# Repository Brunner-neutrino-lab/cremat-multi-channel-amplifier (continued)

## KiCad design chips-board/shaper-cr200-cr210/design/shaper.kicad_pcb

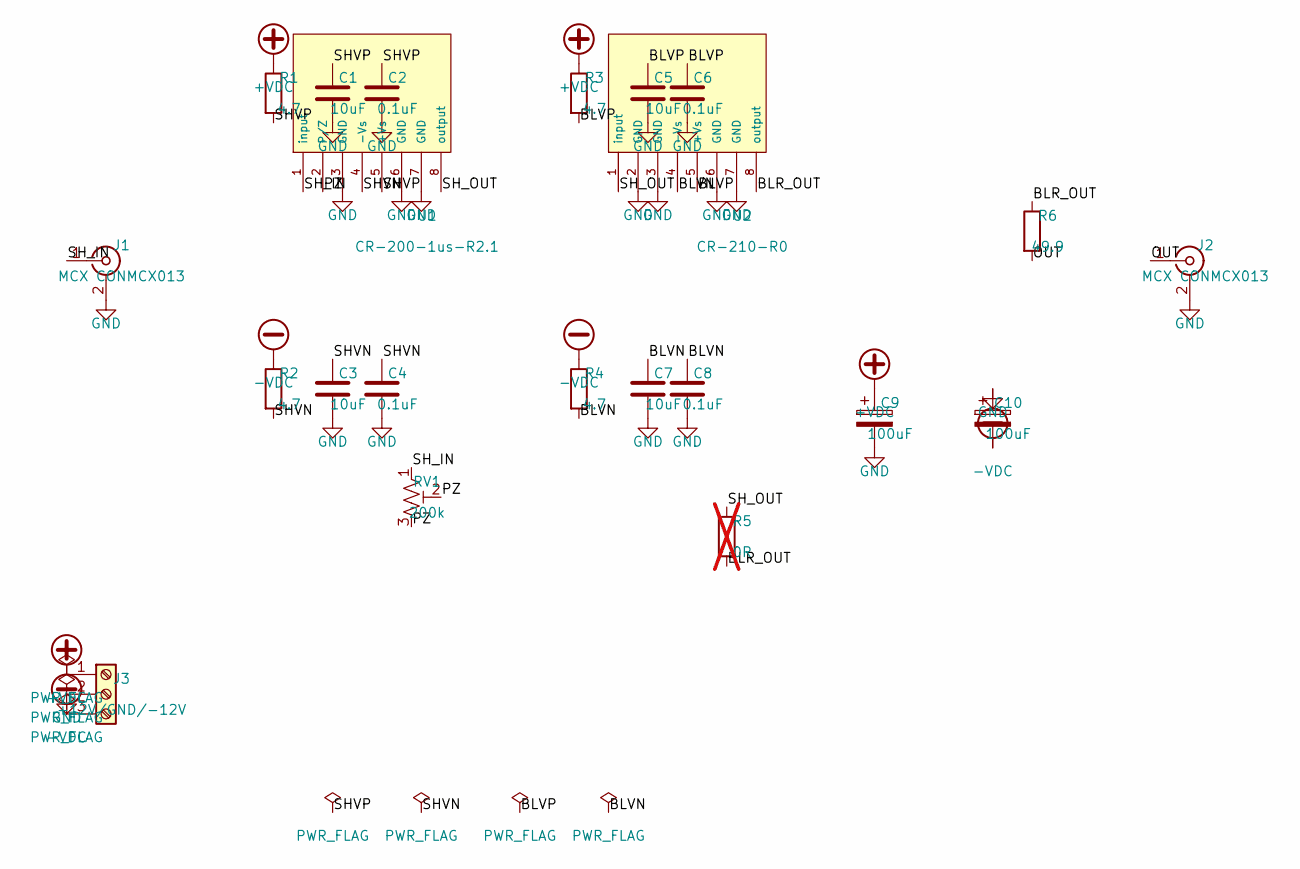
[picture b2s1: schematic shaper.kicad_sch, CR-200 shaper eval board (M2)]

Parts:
C1, C3, C5, C7: 10uF; C_0805_2012Metric; MPN CL21A106KAYNNNE
C2, C4, C6, C8: 0.1uF; C_0805_2012Metric; MPN CL21B104KBCNNNC
C9, C10: 100uF; CP_Elec_6.3x7.7; MPN UWT1V101MCL1GS
J1, J2: MCX CONMCX013; MCX_CONMCX013_EdgeMount; MPN CONMCX013
J3: +12V/GND/-12V; TerminalBlock_Phoenix_MKDS-1,5-3_1x03_P5.00mm_Horizontal; MPN 1715734
R1, R2, R3, R4: 4.7; R_0805_2012Metric; MPN RC0805JR-074R7L
R5: 0R; R_0805_2012Metric; MPN RC0805JR-070RL; not fitted
R6: 49.9; R_0805_2012Metric; MPN RC0805FR-0749R9L
RV1: 200k; Potentiometer_Bourns_3296W_Vertical; MPN 3296W-1-204LF
U1: CR-200-1us-R2.1; PinHeader_1x08_P2.54mm_Vertical; MPN CR-200-1us-R2.1
U2: CR-210-R0; PinHeader_1x08_P2.54mm_Vertical; MPN CR-210-R0

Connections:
+VDC: C9.1, J3.1, R1.1, R3.1
-VDC: C10.2, J3.3, R2.1, R4.1
BLR_OUT: R5.2, R6.1, U2.8 (output)
BLVN: C7.1, C8.1, R4.2, U2.4 (-Vs)
BLVP: C5.1, C6.1, R3.2, U2.5 (+Vs)
GND: C1.2, C2.2, C3.2, C4.2, C5.2, C6.2, C7.2, C8.2, C9.2, C10.1, J1.2 (Ext), J2.2 (Ext), J3.2, U1.3 (GND), U1.6 (GND), U1.7 (GND), U2.2 (GND), U2.3 (GND), U2.6 (GND), U2.7 (GND)
OUT: J2.1 (In), R6.2
PZ: RV1.2, RV1.3, U1.2 (P/Z)
SHVN: C3.1, C4.1, R2.2, U1.4 (-Vs)
SHVP: C1.1, C2.1, R1.2, U1.5 (+Vs)
SH_IN: J1.1 (In), RV1.1, U1.1 (input)
SH_OUT: R5.1, U1.8 (output), U2.1 (input)

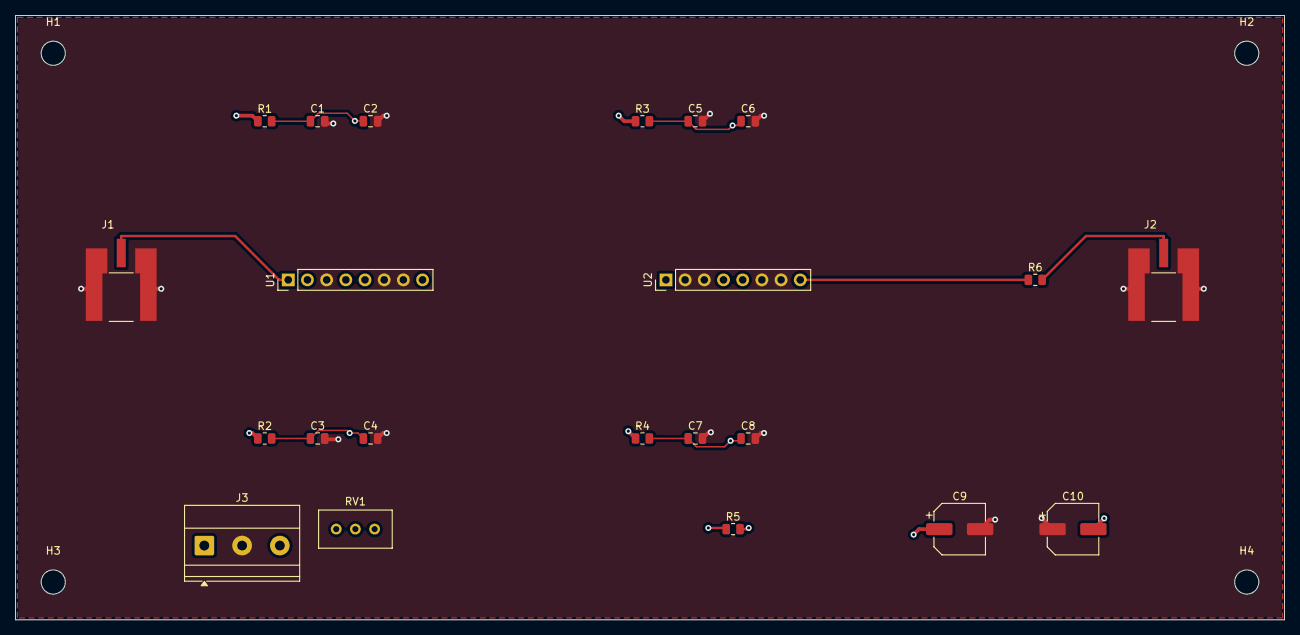
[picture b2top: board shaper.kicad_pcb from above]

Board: 4 copper layers, 168.0 x 80.0 mm, 26 parts (0 on the bottom side), 12 nets.

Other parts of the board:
H1, H2, H3, H4: MountingHole_3.2mm_M3

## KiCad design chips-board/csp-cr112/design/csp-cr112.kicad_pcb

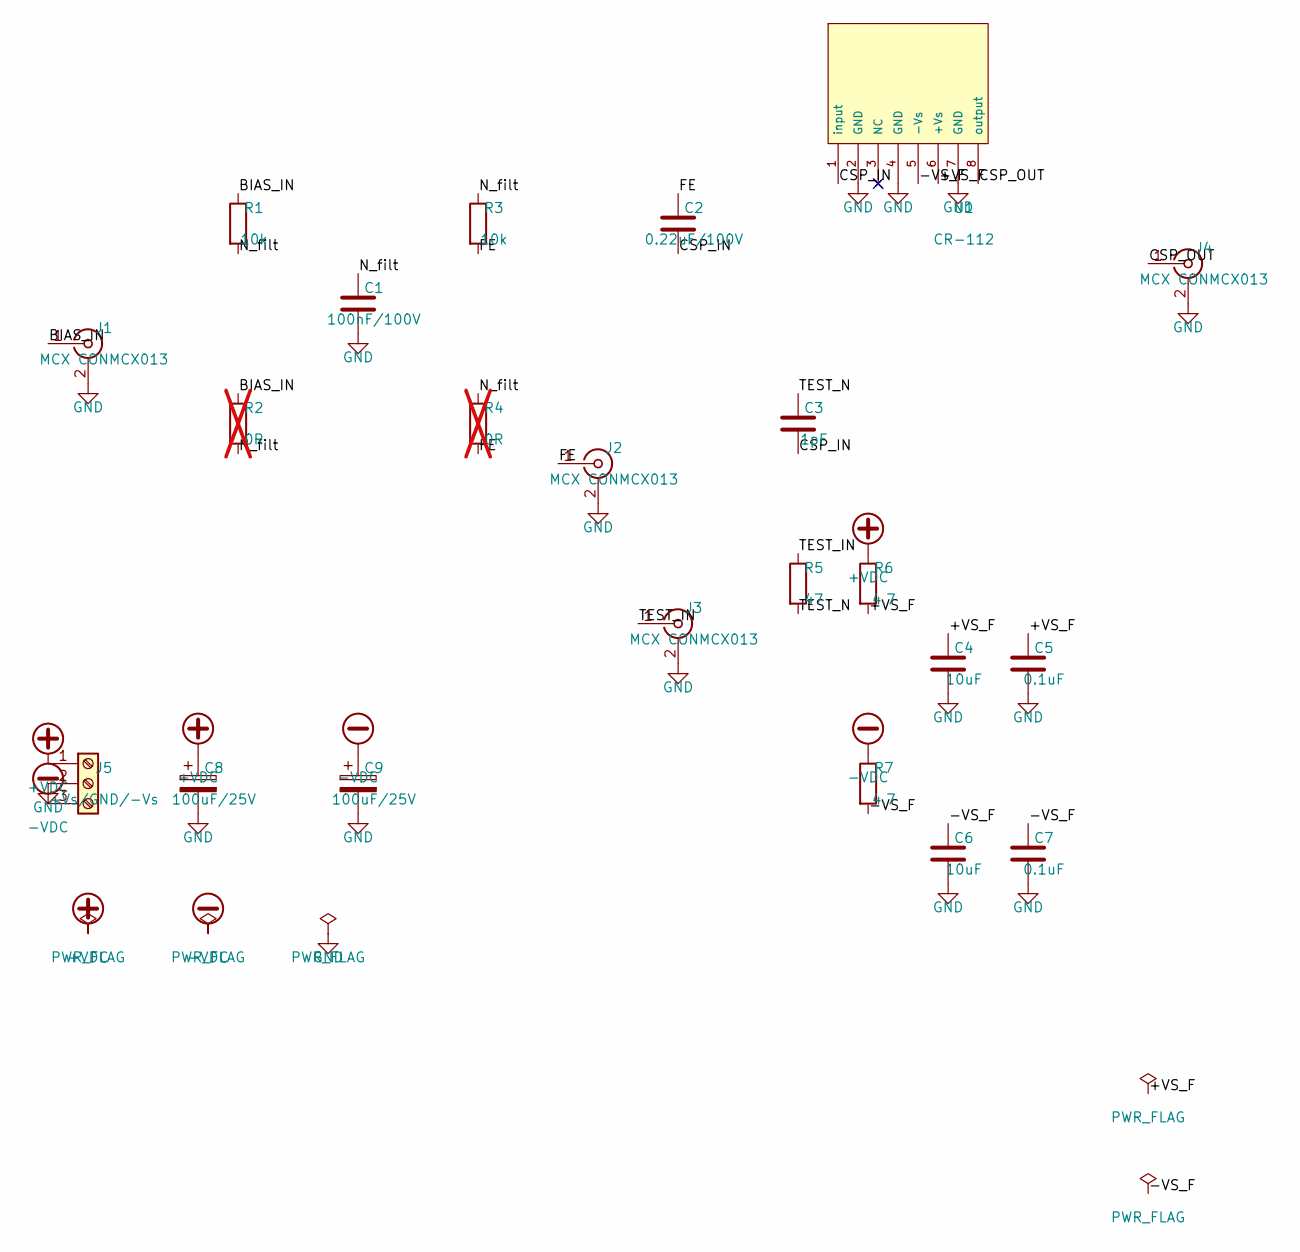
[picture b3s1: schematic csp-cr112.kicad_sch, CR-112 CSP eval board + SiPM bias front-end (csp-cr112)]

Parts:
C1: 100nF/100V; C_0805_2012Metric; MPN CL21B104KCC5PNC
C2: 0.22uF/100V; C_0805_2012Metric; MPN GRM21AR72A224KAC5K
C3: 1pF; C_0805_2012Metric; MPN CC0805CRNPO9BN1R0
C4, C6: 10uF; C_0805_2012Metric; MPN CL21A106KAYNNNE
C5, C7: 0.1uF; C_0805_2012Metric; MPN CL21B104KBCNNNC
C8, C9: 100uF/25V; CP_Radial_D6.3mm_P2.50mm; MPN UVR1E101MED
J1, J2, J3, J4: MCX CONMCX013; MCX_CONMCX013_EdgeMount; MPN CONMCX013
J5: +Vs/GND/-Vs; TerminalBlock_Phoenix_MKDS-1,5-3_1x03_P5.00mm_Horizontal; MPN 1715035
R1, R3: 10k; R_0805_2012Metric; MPN RC0805FR-0710KL
R2, R4: 0R; R_0805_2012Metric; MPN RC0805JR-070RL; not fitted
R5: 47; R_0805_2012Metric; MPN RC0805JR-0747RL
R6, R7: 4.7; R_0805_2012Metric; MPN RC0805JR-074R7L
U1: CR-112; PinHeader_1x08_P2.54mm_Vertical; MPN CR-112-R2.1

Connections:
+VDC: C8.1, J5.1, R6.1
-VDC: C9.1, J5.3, R7.1
/+VS_F: C4.1, C5.1, R6.2, U1.6 (+Vs)
/-VS_F: C6.1, C7.1, R7.2, U1.5 (-Vs)
/BIAS_IN: J1.1 (In), R1.1, R2.1
/CSP_IN: C2.2, C3.2, U1.1 (input)
/CSP_OUT: J4.1 (In), U1.8 (output)
/FE: C2.1, J2.1 (In), R3.2, R4.2
/N_filt: C1.1, R1.2, R2.2, R3.1, R4.1
/TEST_IN: J3.1 (In), R5.1
/TEST_N: C3.1, R5.2
GND: C1.2, C4.2, C5.2, C6.2, C7.2, C8.2, C9.2, J1.2 (Ext), J2.2 (Ext), J3.2 (Ext), J4.2 (Ext), J5.2, U1.2 (GND), U1.4 (GND), U1.7 (GND)

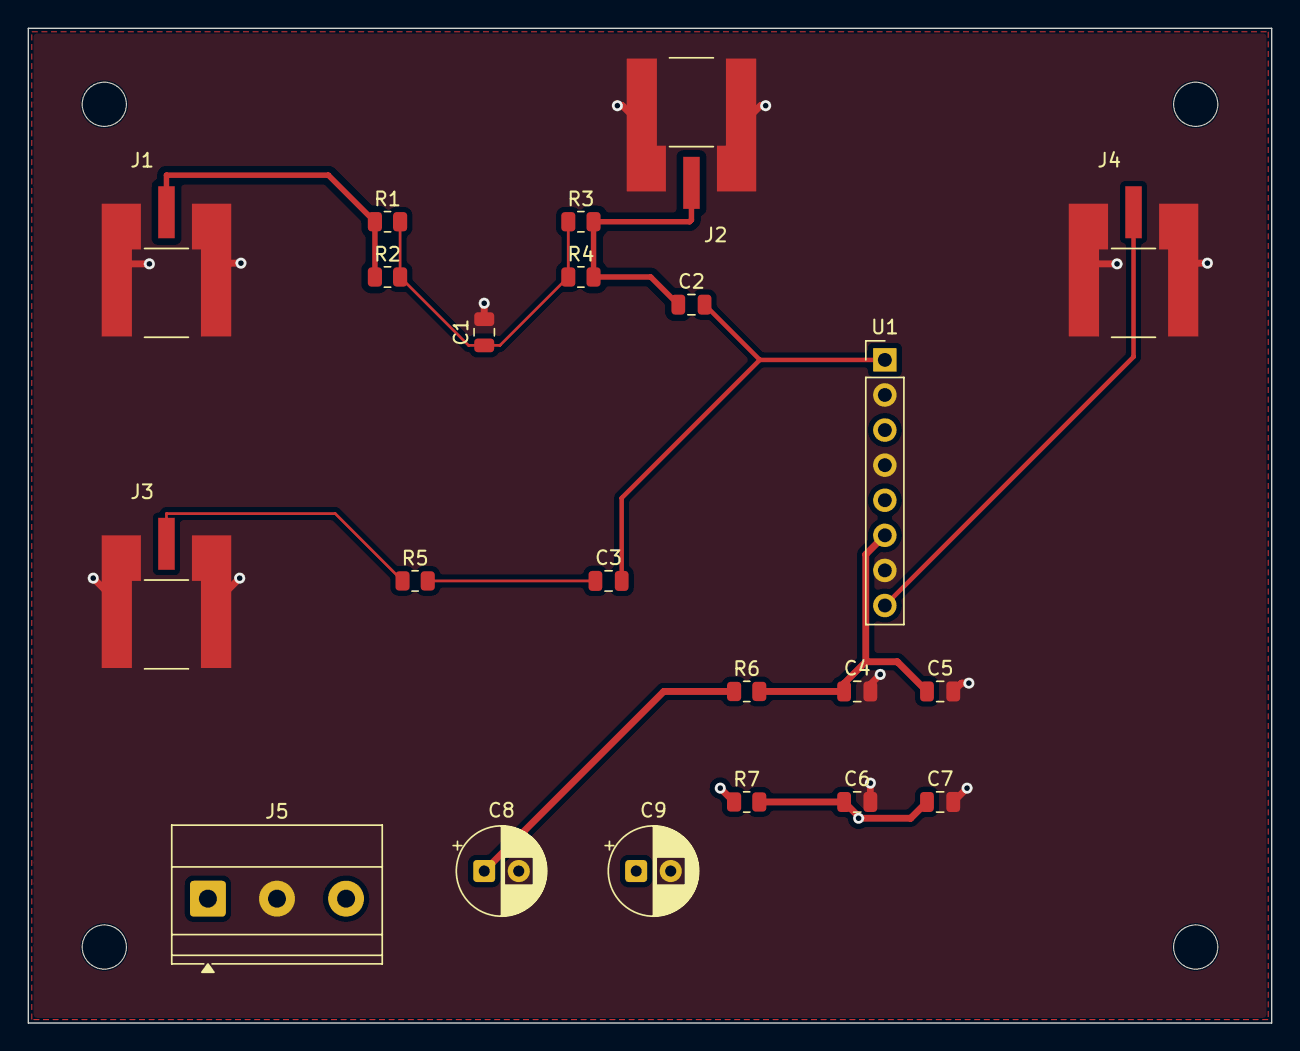
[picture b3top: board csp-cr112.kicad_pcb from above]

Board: 4 copper layers, 90.0 x 72.0 mm, 26 parts (0 on the bottom side), 12 nets.

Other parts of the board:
H1, H2, H3, H4: MountingHole_3.2mm_M3

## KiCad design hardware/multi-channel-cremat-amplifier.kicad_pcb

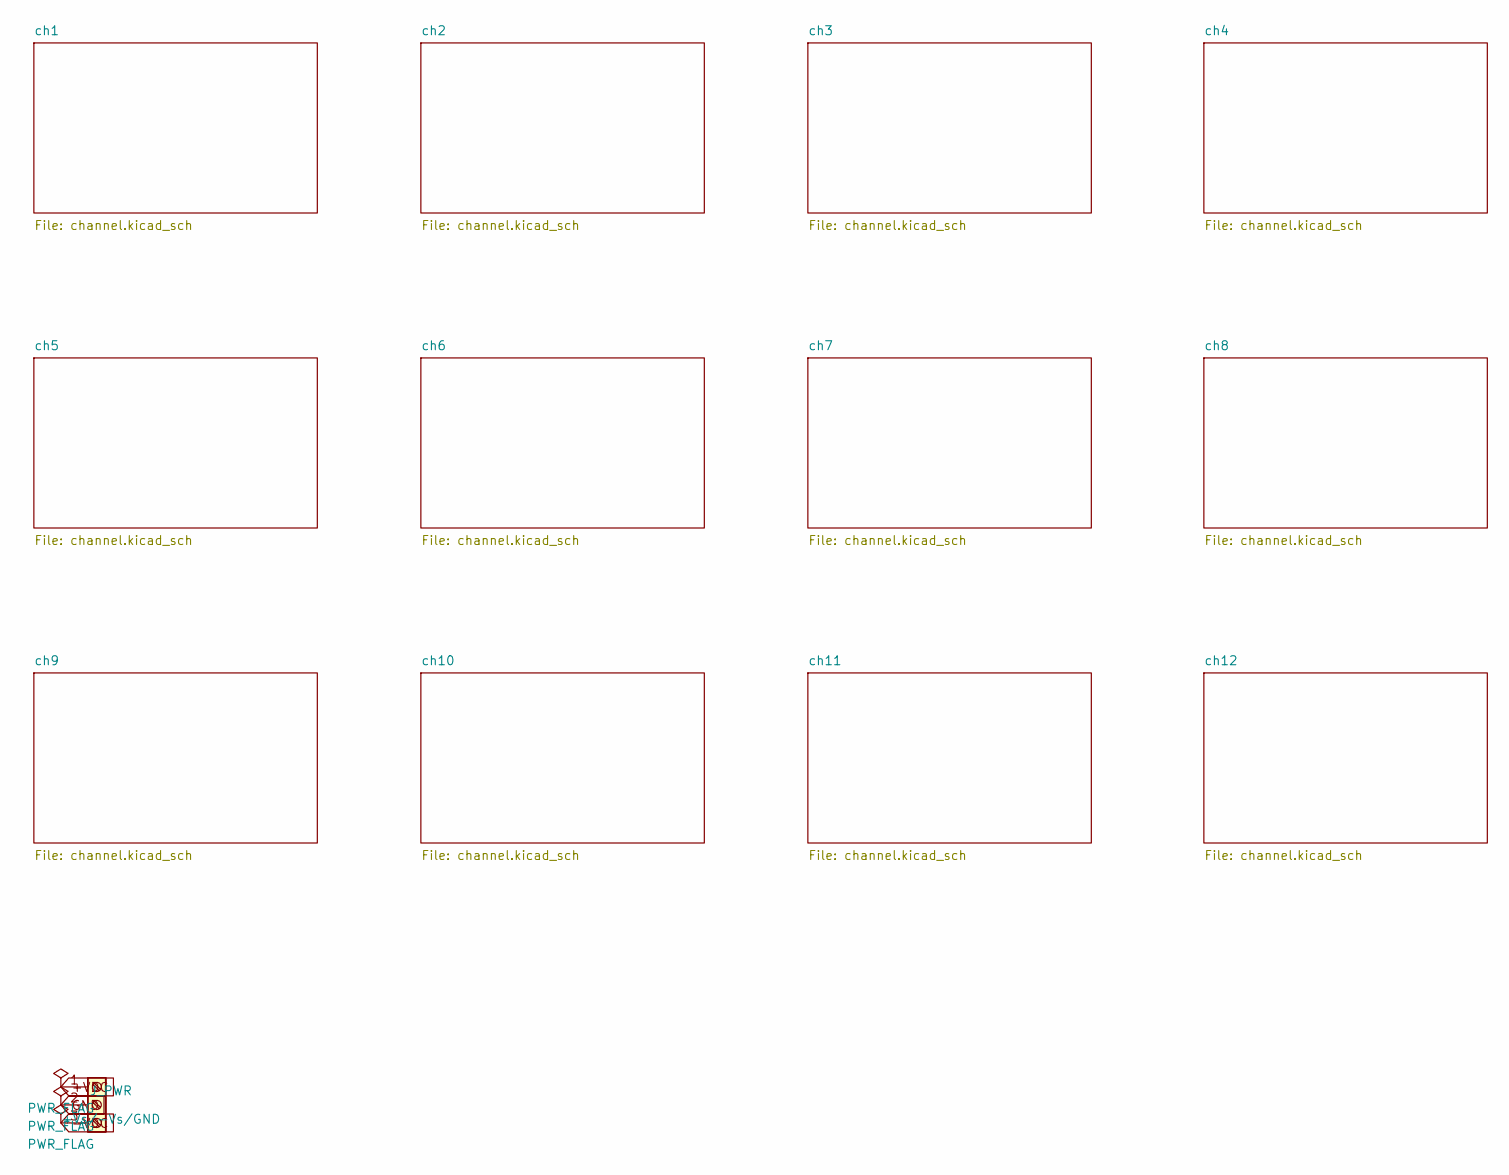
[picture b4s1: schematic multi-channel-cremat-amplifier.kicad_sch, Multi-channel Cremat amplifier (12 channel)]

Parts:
J_PWR: +Vs/-Vs/GND; TerminalBlock_Phoenix_MKDS-1,5-3_1x03_P5.00mm_Horizontal

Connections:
+VDC: J_PWR.1; also elsewhere on the board
-VDC: J_PWR.3; also elsewhere on the board
GND: J_PWR.2; also elsewhere on the board

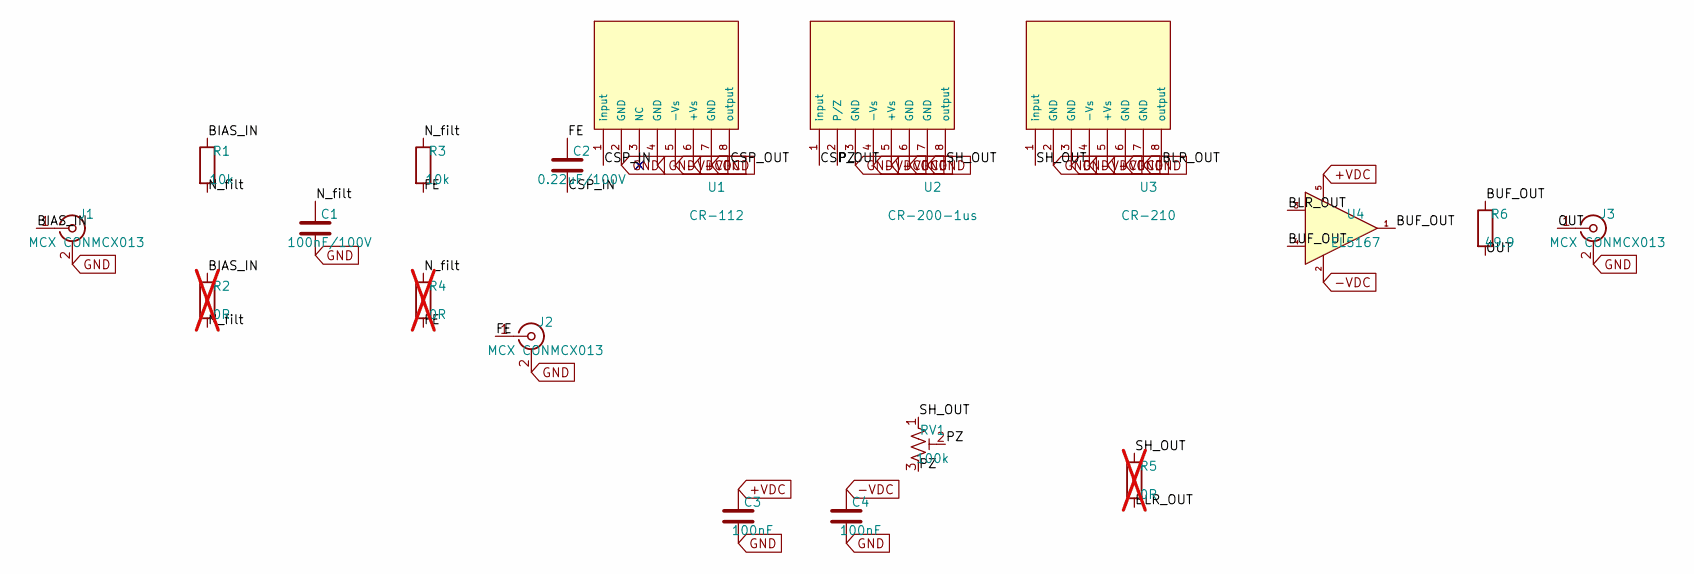
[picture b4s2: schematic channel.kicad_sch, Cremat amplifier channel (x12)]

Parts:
C1: 100nF/100V; C_0805_2012Metric
C2: 0.22uF/100V; C_0805_2012Metric
C3, C4: 100nF; C_0805_2012Metric
J1, J2, J3: MCX CONMCX013; MCX_CONMCX013_EdgeMount
R1, R3: 10k; R_0805_2012Metric
R2, R4, R5: 0R; R_0805_2012Metric; not fitted
R6: 49.9; R_0805_2012Metric
RV1: 100k; Potentiometer_Bourns_3296W_Vertical
U1: CR-112; PinHeader_1x08_P2.54mm_Vertical
U2: CR-200-1us; PinHeader_1x08_P2.54mm_Vertical
U3: CR-210; PinHeader_1x08_P2.54mm_Vertical
U4: EL5167; SOT-23-5

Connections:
+VDC: C3.1, U1.6 (+Vs), U2.5 (+Vs), U3.5 (+Vs), U4.5 (V+); also elsewhere on the board
-VDC: C4.1, U1.5 (-Vs), U2.4 (-Vs), U3.4 (-Vs), U4.2 (V-); also elsewhere on the board
/ch1/BIAS_IN: J1.1 (In), R1.1, R2.1
/ch1/BLR_OUT: R5.2, U3.8 (output), U4.3 (+)
/ch1/BUF_OUT: R6.1, U4.1, U4.4 (-)
/ch1/CSP_IN: C2.2, U1.1 (input)
/ch1/CSP_OUT: U1.8 (output), U2.1 (input)
/ch1/FE: C2.1, J2.1 (In), R3.2, R4.2
/ch1/N_filt: C1.1, R1.2, R2.2, R3.1, R4.1
/ch1/OUT: J3.1 (In), R6.2
/ch1/PZ: RV1.2, RV1.3, U2.2 (P/Z)
/ch1/SH_OUT: R5.1, RV1.1, U2.8 (output), U3.1 (input)
GND: C1.2, C3.2, C4.2, J1.2 (Ext), J2.2 (Ext), J3.2 (Ext), U1.2 (GND), U1.4 (GND), U1.7 (GND), U2.3 (GND), U2.6 (GND), U2.7 (GND), U3.2 (GND), U3.3 (GND), U3.6 (GND), U3.7 (GND); also elsewhere on the board

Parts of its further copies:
C5, C9, C13, C17, C21, C25, C29, C33, C37, C41, C45: 100nF/100V; C_0805_2012Metric
C6, C10, C14, C18, C22, C26, C30, C34, C38, C42, C46: 0.22uF/100V; C_0805_2012Metric
C7, C8, C11, C12, C15, C16, C19, C20, C23, C24, C27, C28, C31, C32, C35, C36, C39, C40, C43, C44, C47, C48: 100nF; C_0805_2012Metric
J4, J5, J6, J7, J8, J9, J10, J11, J12, J13, J14, J15, J16, J17, J18, J19, J20, J21, J22, J23, J24, J25, J26, J27, J28, J29, J30, J31, J32, J33, J34, J35, J36: MCX CONMCX013; MCX_CONMCX013_EdgeMount
R7, R9, R13, R15, R19, R21, R25, R27, R31, R33, R37, R39, R43, R45, R49, R51, R55, R57, R61, R63, R67, R69: 10k; R_0805_2012Metric
R8, R10, R11, R14, R16, R17, R20, R22, R23, R26, R28, R29, R32, R34, R35, R38, R40, R41, R44, R46, R47, R50, R52, R53, R56, R58, R59, R62, R64, R65, R68, R70, R71: 0R; R_0805_2012Metric; not fitted
R12, R18, R24, R30, R36, R42, R48, R54, R60, R66, R72: 49.9; R_0805_2012Metric
RV2, RV3, RV4, RV5, RV6, RV7, RV8, RV9, RV10, RV11, RV12: 100k; Potentiometer_Bourns_3296W_Vertical
U5, U9, U13, U17, U21, U25, U29, U33, U37, U41, U45: CR-112; PinHeader_1x08_P2.54mm_Vertical
U6, U10, U14, U18, U22, U26, U30, U34, U38, U42, U46: CR-200-1us; PinHeader_1x08_P2.54mm_Vertical
U7, U11, U15, U19, U23, U27, U31, U35, U39, U43, U47: CR-210; PinHeader_1x08_P2.54mm_Vertical
U8, U12, U16, U20, U24, U28, U32, U36, U40, U44, U48: EL5167; SOT-23-5

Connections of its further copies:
+VDC: C7.1, C11.1, C15.1, C19.1, C23.1, C27.1, C31.1, C35.1, C39.1, C43.1, C47.1, U5.6 (+Vs), U6.5 (+Vs), U7.5 (+Vs), U8.5 (V+), U9.6 (+Vs), U10.5 (+Vs), U11.5 (+Vs), U12.5 (V+), U13.6 (+Vs), U14.5 (+Vs), U15.5 (+Vs), U16.5 (V+), U17.6 (+Vs), U18.5 (+Vs), U19.5 (+Vs), U20.5 (V+), U21.6 (+Vs), U22.5 (+Vs), U23.5 (+Vs), U24.5 (V+), U25.6 (+Vs), U26.5 (+Vs), U27.5 (+Vs), U28.5 (V+), U29.6 (+Vs), U30.5 (+Vs), U31.5 (+Vs), U32.5 (V+), U33.6 (+Vs), U34.5 (+Vs), U35.5 (+Vs), U36.5 (V+), U37.6 (+Vs), U38.5 (+Vs), U39.5 (+Vs), U40.5 (V+), U41.6 (+Vs), U42.5 (+Vs), U43.5 (+Vs), U44.5 (V+), U45.6 (+Vs), U46.5 (+Vs), U47.5 (+Vs), U48.5 (V+); also elsewhere on the board
-VDC: C8.1, C12.1, C16.1, C20.1, C24.1, C28.1, C32.1, C36.1, C40.1, C44.1, C48.1, U5.5 (-Vs), U6.4 (-Vs), U7.4 (-Vs), U8.2 (V-), U9.5 (-Vs), U10.4 (-Vs), U11.4 (-Vs), U12.2 (V-), U13.5 (-Vs), U14.4 (-Vs), U15.4 (-Vs), U16.2 (V-), U17.5 (-Vs), U18.4 (-Vs), U19.4 (-Vs), U20.2 (V-), U21.5 (-Vs), U22.4 (-Vs), U23.4 (-Vs), U24.2 (V-), U25.5 (-Vs), U26.4 (-Vs), U27.4 (-Vs), U28.2 (V-), U29.5 (-Vs), U30.4 (-Vs), U31.4 (-Vs), U32.2 (V-), U33.5 (-Vs), U34.4 (-Vs), U35.4 (-Vs), U36.2 (V-), U37.5 (-Vs), U38.4 (-Vs), U39.4 (-Vs), U40.2 (V-), U41.5 (-Vs), U42.4 (-Vs), U43.4 (-Vs), U44.2 (V-), U45.5 (-Vs), U46.4 (-Vs), U47.4 (-Vs), U48.2 (V-); also elsewhere on the board
/ch2/BIAS_IN: J4.1 (In), R7.1, R8.1
/ch2/BLR_OUT: R11.2, U7.8 (output), U8.3 (+)
/ch2/BUF_OUT: R12.1, U8.1, U8.4 (-)
/ch2/CSP_IN: C6.2, U5.1 (input)
/ch2/CSP_OUT: U5.8 (output), U6.1 (input)
/ch2/FE: C6.1, J5.1 (In), R9.2, R10.2
/ch2/N_filt: C5.1, R7.2, R8.2, R9.1, R10.1
/ch2/OUT: J6.1 (In), R12.2
/ch2/PZ: RV2.2, RV2.3, U6.2 (P/Z)
/ch2/SH_OUT: R11.1, RV2.1, U6.8 (output), U7.1 (input)
/ch3/BIAS_IN: J7.1 (In), R13.1, R14.1
/ch3/BLR_OUT: R17.2, U11.8 (output), U12.3 (+)
/ch3/BUF_OUT: R18.1, U12.1, U12.4 (-)
/ch3/CSP_IN: C10.2, U9.1 (input)
/ch3/CSP_OUT: U9.8 (output), U10.1 (input)
/ch3/FE: C10.1, J8.1 (In), R15.2, R16.2
/ch3/N_filt: C9.1, R13.2, R14.2, R15.1, R16.1
/ch3/OUT: J9.1 (In), R18.2
/ch3/PZ: RV3.2, RV3.3, U10.2 (P/Z)
/ch3/SH_OUT: R17.1, RV3.1, U10.8 (output), U11.1 (input)
/ch4/BIAS_IN: J10.1 (In), R19.1, R20.1
/ch4/BLR_OUT: R23.2, U15.8 (output), U16.3 (+)
/ch4/BUF_OUT: R24.1, U16.1, U16.4 (-)
/ch4/CSP_IN: C14.2, U13.1 (input)
/ch4/CSP_OUT: U13.8 (output), U14.1 (input)
/ch4/FE: C14.1, J11.1 (In), R21.2, R22.2
/ch4/N_filt: C13.1, R19.2, R20.2, R21.1, R22.1
/ch4/OUT: J12.1 (In), R24.2
/ch4/PZ: RV4.2, RV4.3, U14.2 (P/Z)
/ch4/SH_OUT: R23.1, RV4.1, U14.8 (output), U15.1 (input)
/ch5/BIAS_IN: J13.1 (In), R25.1, R26.1
/ch5/BLR_OUT: R29.2, U19.8 (output), U20.3 (+)
/ch5/BUF_OUT: R30.1, U20.1, U20.4 (-)
/ch5/CSP_IN: C18.2, U17.1 (input)
/ch5/CSP_OUT: U17.8 (output), U18.1 (input)
/ch5/FE: C18.1, J14.1 (In), R27.2, R28.2
/ch5/N_filt: C17.1, R25.2, R26.2, R27.1, R28.1
/ch5/OUT: J15.1 (In), R30.2
/ch5/PZ: RV5.2, RV5.3, U18.2 (P/Z)
/ch5/SH_OUT: R29.1, RV5.1, U18.8 (output), U19.1 (input)
/ch6/BIAS_IN: J16.1 (In), R31.1, R32.1
/ch6/BLR_OUT: R35.2, U23.8 (output), U24.3 (+)
/ch6/BUF_OUT: R36.1, U24.1, U24.4 (-)
/ch6/CSP_IN: C22.2, U21.1 (input)
/ch6/CSP_OUT: U21.8 (output), U22.1 (input)
/ch6/FE: C22.1, J17.1 (In), R33.2, R34.2
/ch6/N_filt: C21.1, R31.2, R32.2, R33.1, R34.1
/ch6/OUT: J18.1 (In), R36.2
/ch6/PZ: RV6.2, RV6.3, U22.2 (P/Z)
/ch6/SH_OUT: R35.1, RV6.1, U22.8 (output), U23.1 (input)
/ch7/BIAS_IN: J19.1 (In), R37.1, R38.1
/ch7/BLR_OUT: R41.2, U27.8 (output), U28.3 (+)
/ch7/BUF_OUT: R42.1, U28.1, U28.4 (-)
/ch7/CSP_IN: C26.2, U25.1 (input)
/ch7/CSP_OUT: U25.8 (output), U26.1 (input)
/ch7/FE: C26.1, J20.1 (In), R39.2, R40.2
/ch7/N_filt: C25.1, R37.2, R38.2, R39.1, R40.1
/ch7/OUT: J21.1 (In), R42.2
/ch7/PZ: RV7.2, RV7.3, U26.2 (P/Z)
/ch7/SH_OUT: R41.1, RV7.1, U26.8 (output), U27.1 (input)
/ch8/BIAS_IN: J22.1 (In), R43.1, R44.1
/ch8/BLR_OUT: R47.2, U31.8 (output), U32.3 (+)
/ch8/BUF_OUT: R48.1, U32.1, U32.4 (-)
/ch8/CSP_IN: C30.2, U29.1 (input)
/ch8/CSP_OUT: U29.8 (output), U30.1 (input)
/ch8/FE: C30.1, J23.1 (In), R45.2, R46.2
/ch8/N_filt: C29.1, R43.2, R44.2, R45.1, R46.1
/ch8/OUT: J24.1 (In), R48.2
/ch8/PZ: RV8.2, RV8.3, U30.2 (P/Z)
/ch8/SH_OUT: R47.1, RV8.1, U30.8 (output), U31.1 (input)
/ch9/BIAS_IN: J25.1 (In), R49.1, R50.1
/ch9/BLR_OUT: R53.2, U35.8 (output), U36.3 (+)
/ch9/BUF_OUT: R54.1, U36.1, U36.4 (-)
/ch9/CSP_IN: C34.2, U33.1 (input)
/ch9/CSP_OUT: U33.8 (output), U34.1 (input)
/ch9/FE: C34.1, J26.1 (In), R51.2, R52.2
/ch9/N_filt: C33.1, R49.2, R50.2, R51.1, R52.1
/ch9/OUT: J27.1 (In), R54.2
/ch9/PZ: RV9.2, RV9.3, U34.2 (P/Z)
/ch9/SH_OUT: R53.1, RV9.1, U34.8 (output), U35.1 (input)
/ch10/BIAS_IN: J28.1 (In), R55.1, R56.1
/ch10/BLR_OUT: R59.2, U39.8 (output), U40.3 (+)
/ch10/BUF_OUT: R60.1, U40.1, U40.4 (-)
/ch10/CSP_IN: C38.2, U37.1 (input)
/ch10/CSP_OUT: U37.8 (output), U38.1 (input)
/ch10/FE: C38.1, J29.1 (In), R57.2, R58.2
/ch10/N_filt: C37.1, R55.2, R56.2, R57.1, R58.1
/ch10/OUT: J30.1 (In), R60.2
/ch10/PZ: RV10.2, RV10.3, U38.2 (P/Z)
/ch10/SH_OUT: R59.1, RV10.1, U38.8 (output), U39.1 (input)
/ch11/BIAS_IN: J31.1 (In), R61.1, R62.1
/ch11/BLR_OUT: R65.2, U43.8 (output), U44.3 (+)
/ch11/BUF_OUT: R66.1, U44.1, U44.4 (-)
/ch11/CSP_IN: C42.2, U41.1 (input)
/ch11/CSP_OUT: U41.8 (output), U42.1 (input)
/ch11/FE: C42.1, J32.1 (In), R63.2, R64.2
/ch11/N_filt: C41.1, R61.2, R62.2, R63.1, R64.1
/ch11/OUT: J33.1 (In), R66.2
/ch11/PZ: RV11.2, RV11.3, U42.2 (P/Z)
/ch11/SH_OUT: R65.1, RV11.1, U42.8 (output), U43.1 (input)
/ch12/BIAS_IN: J34.1 (In), R67.1, R68.1
/ch12/BLR_OUT: R71.2, U47.8 (output), U48.3 (+)
/ch12/BUF_OUT: R72.1, U48.1, U48.4 (-)
/ch12/CSP_IN: C46.2, U45.1 (input)
/ch12/CSP_OUT: U45.8 (output), U46.1 (input)
/ch12/FE: C46.1, J35.1 (In), R69.2, R70.2
/ch12/N_filt: C45.1, R67.2, R68.2, R69.1, R70.1
/ch12/OUT: J36.1 (In), R72.2
/ch12/PZ: RV12.2, RV12.3, U46.2 (P/Z)
/ch12/SH_OUT: R71.1, RV12.1, U46.8 (output), U47.1 (input)
GND: C5.2, C7.2, C8.2, C9.2, C11.2, C12.2, C13.2, C15.2, C16.2, C17.2, C19.2, C20.2, C21.2, C23.2, C24.2, C25.2, C27.2, C28.2, C29.2, C31.2, C32.2, C33.2, C35.2, C36.2, C37.2, C39.2, C40.2, C41.2, C43.2, C44.2, C45.2, C47.2, C48.2, J4.2 (Ext), J5.2 (Ext), J6.2 (Ext), J7.2 (Ext), J8.2 (Ext), J9.2 (Ext), J10.2 (Ext), J11.2 (Ext), J12.2 (Ext), J13.2 (Ext), J14.2 (Ext), J15.2 (Ext), J16.2 (Ext), J17.2 (Ext), J18.2 (Ext), J19.2 (Ext), J20.2 (Ext), J21.2 (Ext), J22.2 (Ext), J23.2 (Ext), J24.2 (Ext), J25.2 (Ext), J26.2 (Ext), J27.2 (Ext), J28.2 (Ext), J29.2 (Ext), J30.2 (Ext), J31.2 (Ext), J32.2 (Ext), J33.2 (Ext), J34.2 (Ext), J35.2 (Ext), J36.2 (Ext), U5.2 (GND), U5.4 (GND), U5.7 (GND), U6.3 (GND), U6.6 (GND), U6.7 (GND), U7.2 (GND), U7.3 (GND), U7.6 (GND), U7.7 (GND), U9.2 (GND), U9.4 (GND), U9.7 (GND), U10.3 (GND), U10.6 (GND), U10.7 (GND), U11.2 (GND), U11.3 (GND), U11.6 (GND), U11.7 (GND), U13.2 (GND), U13.4 (GND), U13.7 (GND), U14.3 (GND), U14.6 (GND), U14.7 (GND), U15.2 (GND), U15.3 (GND), U15.6 (GND), U15.7 (GND), U17.2 (GND), U17.4 (GND), U17.7 (GND), U18.3 (GND), U18.6 (GND), U18.7 (GND), U19.2 (GND), U19.3 (GND), U19.6 (GND), U19.7 (GND), U21.2 (GND), U21.4 (GND), U21.7 (GND), U22.3 (GND), U22.6 (GND), U22.7 (GND), U23.2 (GND), U23.3 (GND), U23.6 (GND), U23.7 (GND), U25.2 (GND), U25.4 (GND), U25.7 (GND), U26.3 (GND), U26.6 (GND), U26.7 (GND), U27.2 (GND), U27.3 (GND), U27.6 (GND), U27.7 (GND), U29.2 (GND), U29.4 (GND), U29.7 (GND), U30.3 (GND), U30.6 (GND), U30.7 (GND), U31.2 (GND), U31.3 (GND), U31.6 (GND), U31.7 (GND), U33.2 (GND), U33.4 (GND), U33.7 (GND), U34.3 (GND), U34.6 (GND), U34.7 (GND), U35.2 (GND), U35.3 (GND), U35.6 (GND), U35.7 (GND), U37.2 (GND), U37.4 (GND), U37.7 (GND), U38.3 (GND), U38.6 (GND), U38.7 (GND), U39.2 (GND), U39.3 (GND), U39.6 (GND), U39.7 (GND), U41.2 (GND), U41.4 (GND), U41.7 (GND), U42.3 (GND), U42.6 (GND), U42.7 (GND), U43.2 (GND), U43.3 (GND), U43.6 (GND), U43.7 (GND), U45.2 (GND), U45.4 (GND), U45.7 (GND), U46.3 (GND), U46.6 (GND), U46.7 (GND), U47.2 (GND), U47.3 (GND), U47.6 (GND), U47.7 (GND); also elsewhere on the board

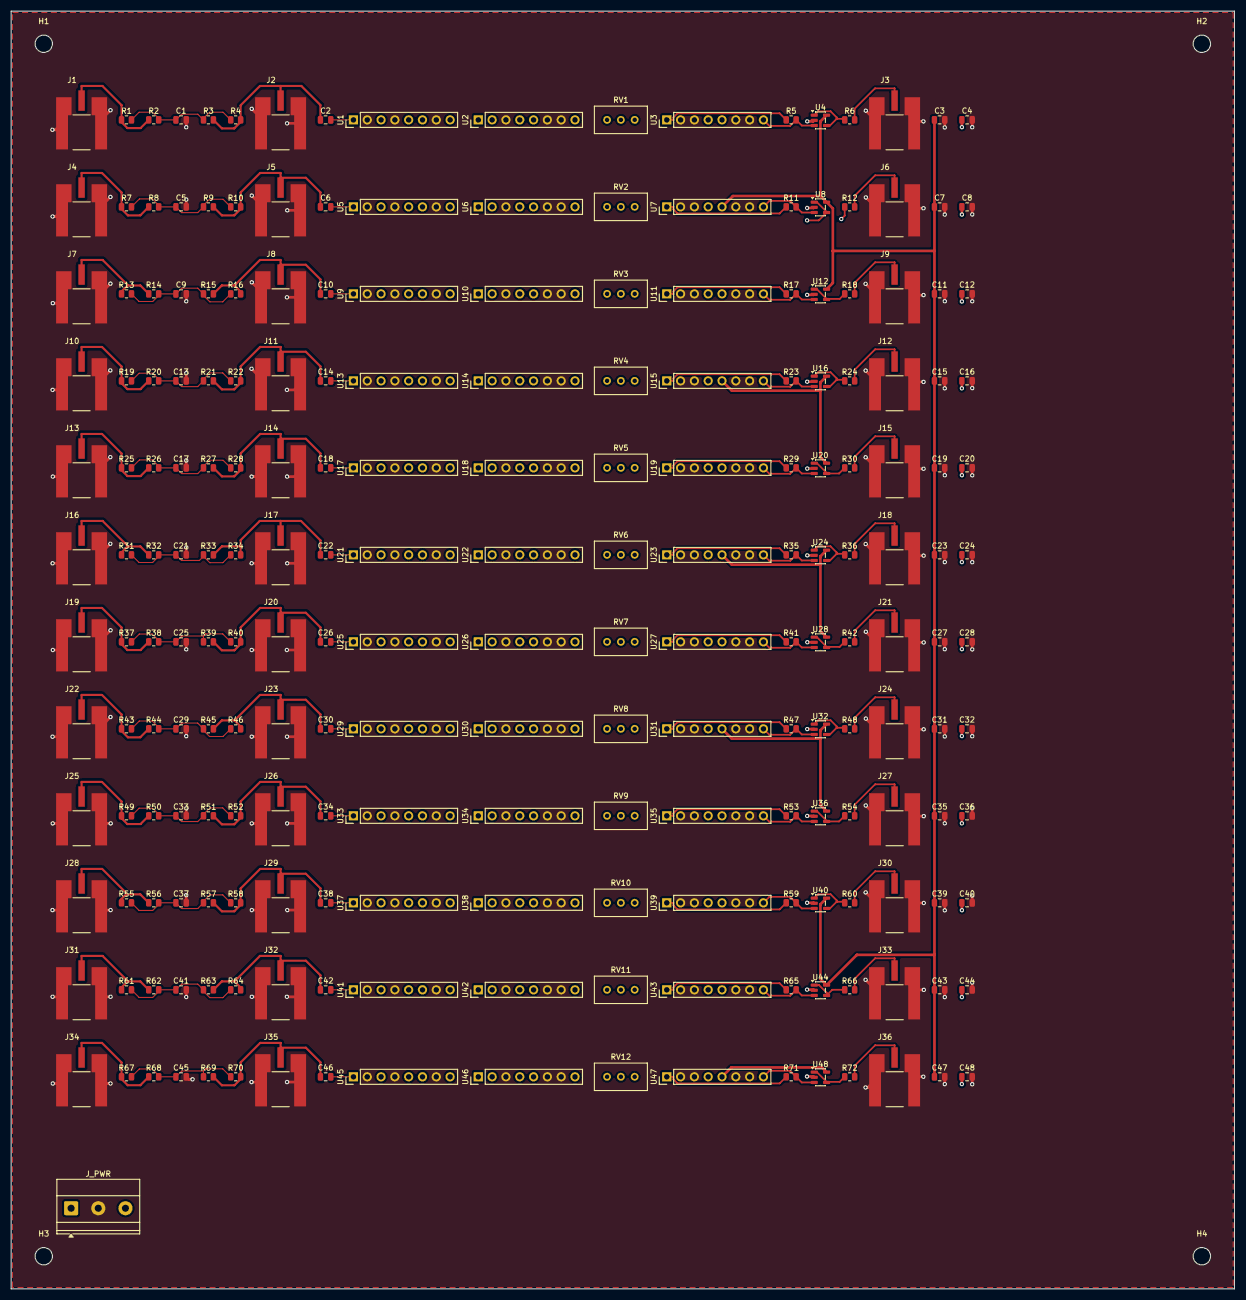
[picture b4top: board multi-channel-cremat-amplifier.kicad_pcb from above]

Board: 4 copper layers, 225.0 x 235.0 mm, 221 parts (0 on the bottom side), 123 nets.

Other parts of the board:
H1, H2, H3, H4: MountingHole_3.2mm_M3

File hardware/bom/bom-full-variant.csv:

Ref,Value,Footprint,MPN_or_Source,Qty_per_channel,Qty_x12,Populate_Full,Notes
U_CSP,CR-112,Connector_PinHeader_2.54mm:PinHeader_1x08_P2.54mm_Vertical,Cremat CR-112,1,12,Y,Charge-sensitive preamp (SIP-8)
U_SHAPER,CR-200-1us,Connector_PinHeader_2.54mm:PinHeader_1x08_P2.54mm_Vertical,Cremat CR-200-1us,1,12,Y,Gaussian shaper 1us (SIP-8)
U_BLR,CR-210,Connector_PinHeader_2.54mm:PinHeader_1x08_P2.54mm_Vertical,Cremat CR-210,1,12,Y,Baseline restorer (SIP-8); optional
U_BUF,EL5167,Package_TO_SOT_SMD:SOT-23-5,Renesas EL5167 / TI LM7321,1,12,Y,Output buffer / line driver
Cc,0.22uF 100V X5R,Capacitor_SMD:C_0805_2012Metric,100V 0805 MLCC,1,12,Y,AC coupling; HV (>=bias)
Rf1,10k,Resistor_SMD:R_0805_2012Metric,10k 1% 0805,1,12,Y,Bias filter series R
Rf2,10k,Resistor_SMD:R_0805_2012Metric,10k 1% 0805,1,12,Y,Bias filter series R (SiPM-side)
Cf,100nF 100V X7R,Capacitor_SMD:C_0805_2012Metric,100V 0805 MLCC,1,12,Y,Bias filter shunt C
JP_Rf1,0R,Resistor_SMD:R_0805_2012Metric,0R 0805,1,12,N,Bias-filter bypass (DNP in Full)
JP_Rf2,0R,Resistor_SMD:R_0805_2012Metric,0R 0805,1,12,N,Bias-filter bypass (DNP in Full)
JP_BLR,0R,Resistor_SMD:R_0805_2012Metric,0R 0805,1,12,N,CR-210 bypass (DNP in Full)
R_OUT,49.9,Resistor_SMD:R_0805_2012Metric,49.9R 1% 0805,1,12,Y,50ohm source termination
RV_PZ,100k,Potentiometer_THT:Potentiometer_Bourns_3296W_Vertical,Bourns 3296W-104,1,12,Y,Pole-zero trim
RV_GAIN,per reference,Potentiometer_THT:Potentiometer_Bourns_3296W_Vertical,per reference,1,12,Y,Buffer gain trim
RV_OFS,per reference,Potentiometer_THT:Potentiometer_Bourns_3296W_Vertical,per reference,1,12,Y,Buffer offset trim
J_BIAS,MCX,cremat:MCX_CONMCX013_EdgeMount,TE Linx CONMCX013 (343-CONMCX013-ND),1,12,Y,Per-channel HV bias in (TO CREATE footprint)
J_SIPM,MCX,cremat:MCX_CONMCX013_EdgeMount,TE Linx CONMCX013 (343-CONMCX013-ND),1,12,Y,Per-channel detector (DC bias+signal)
J_OUT,MCX,cremat:MCX_CONMCX013_EdgeMount,TE Linx CONMCX013 (343-CONMCX013-ND),1,12,Y,Per-channel shaped output
J_PWR,Screw terminal 3pos,"TerminalBlock_Phoenix:TerminalBlock_Phoenix_MKDS-1,5-3_1x03_P5.00mm_Horizontal",Phoenix MKDS 1.5/3,1,1,Y,Shared +Vs/-Vs/GND

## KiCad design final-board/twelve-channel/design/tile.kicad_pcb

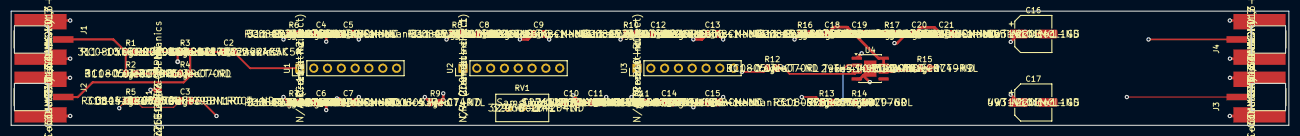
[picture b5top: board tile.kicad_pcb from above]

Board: 4 copper layers, 235.0 x 21.0 mm, 47 parts (0 on the bottom side), 24 nets.

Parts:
C1: 100nF 100V X7R; C_0805_2012Metric
C2: 0.22uF 100V X7R; C_0805_2012Metric
C3: 1pF 50V C0G; C_0805_2012Metric
C4, C6, C8, C10, C12, C14, C18, C20: 10uF 25V X5R; C_0805_2012Metric
C5, C7, C9, C11, C13, C15, C19, C21: 0.1uF 50V X7R; C_0805_2012Metric
C16, C17: 100uF 35V; CP_Elec_6.3x7.7
J1, J2, J3, J4: MCX edge jack 50R; MCX_CONMCX013_EdgeMount
R1, R3: 10k; R_0805_2012Metric
R2, R4, R12: 0R; R_0805_2012Metric
R5: 47; R_0805_2012Metric
R6, R7, R8, R9, R10, R11, R16, R17: 4.7; R_0805_2012Metric
R13, R14: 976; R_0805_2012Metric
R15: 49.9; R_0805_2012Metric
RV1: 200k; Potentiometer_Bourns_3296W_Vertical
U1: CR-112; PinHeader_1x08_P2.54mm_Vertical
U2: CR-200-1us; PinHeader_1x08_P2.54mm_Vertical
U3: CR-210; PinHeader_1x08_P2.54mm_Vertical
U4: THS3491; SOIC-8-1EP_3.9x4.9mm_P1.27mm_EP2.29x3mm

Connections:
+VDC: C16.1, R6.1, R8.1, R10.1, R16.1
-VDC: C17.2, R7.1, R9.1, R11.1, R17.1
/+VS_F_ch01: C4.1, C5.1, R6.2, U1.6
/-VS_F_ch01: C6.1, C7.1, R7.2, U1.5
/BIAS_IN_ch01: J1.1, R1.1, R2.1
/BLVN_ch01: C14.1, C15.1, R11.2, U3.4
/BLVP_ch01: C12.1, C13.1, R10.2, U3.5
/BUF_FB_ch01: R13.2, R14.1, U4.2
/BUF_OUT_ch01: R13.1, R15.1, U4.6
/BVN_ch01: C20.1, C21.1, R17.2, U4.4, U4.9
/BVP_ch01: C18.1, C19.1, R16.2, U4.7, U4.8
/CSP_IN_ch01: C2.2, C3.2, U1.1
/CSP_OUT_ch01: RV1.1, U1.8, U2.1
/FE_ch01: C2.1, J2.1, R3.2, R4.2
/N_filt_ch01: C1.1, R1.2, R2.2, R3.1, R4.1
/OUT_50_ch01: J4.1, R15.2
/PZ_ch01: RV1.2, RV1.3, U2.2
/SHAPER_OUT_ch01: R12.2, U3.8, U4.3
/SHVN_ch01: C10.1, C11.1, R9.2, U2.4
/SHVP_ch01: C8.1, C9.1, R8.2, U2.5
/SH_OUT_ch01: R12.1, U2.8, U3.1
/TEST_IN_ch01: J3.1, R5.1
/TEST_N_ch01: C3.1, R5.2
GND: C1.2, C4.2, C5.2, C6.2, C7.2, C8.2, C9.2, C10.2, C11.2, C12.2, C13.2, C14.2, C15.2, C16.2, C17.1, C18.2, C19.2, C20.2, C21.2, J1.2, J2.2, J3.2, J4.2, R14.2, U1.2, U1.4, U1.7, U2.3, U2.6, U2.7, U3.2, U3.3, U3.6, U3.7, U4.1

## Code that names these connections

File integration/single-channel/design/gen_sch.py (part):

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    # N_filt: Rf1 -> Rf2, Cf tap down, JP_Rf1/JP_Rf2 bypass taps up
    _fx, _fy = P("Cf", "1")[0], P("Rf1", "2")[1]       # N_filt run, SPLIT at the Cf tap
    W(P("Rf1", "2"), (_fx, _fy), P("Rf2", "1"))
    W(P("Cf", "1"), (_fx, _fy))                        # Cf top pin -> stub up -> T into N_filt
    W(P("Rf1", "2"), P("JP_Rf1", "2")); W(P("Rf2", "1"), P("JP_Rf2", "1"))
    pwr("GND", P("Cf", "2"))
    lbl("N_filt", P("Cf", "1"))
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
    # ===== CR-200 shaper =====
    gnd_bus("U_SH", ["3", "6", "7"], 128.27, sym_x=P("U_SH", "7")[0])
    rail_labels("U_SH", "4", "SHVN", "5", "SHVP")
    deco("R_SHP", "C_SHPb", "SHVP", "+VDC", top=True)
    deco("R_SHN", "C_SHNb", "SHVN", "-VDC", top=False)
    # P/Z: U_SH.2 down to wiper, wiper<->bottom tied
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
    # ===== CR-210 BLR =====
    gnd_bus("U_BLR", ["2", "3", "6", "7"], 128.27, sym_x=P("U_BLR", "7")[0])
    rail_labels("U_BLR", "4", "BLVN", "5", "BLVP")
    deco("R_BLP", "C_BLPb", "BLVP", "+VDC", top=True)
    deco("R_BLN", "C_BLNb", "BLVN", "-VDC", top=False)

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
